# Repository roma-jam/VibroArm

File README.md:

# Vibro Watch
Contains fw and hw part of the vibro watch project.

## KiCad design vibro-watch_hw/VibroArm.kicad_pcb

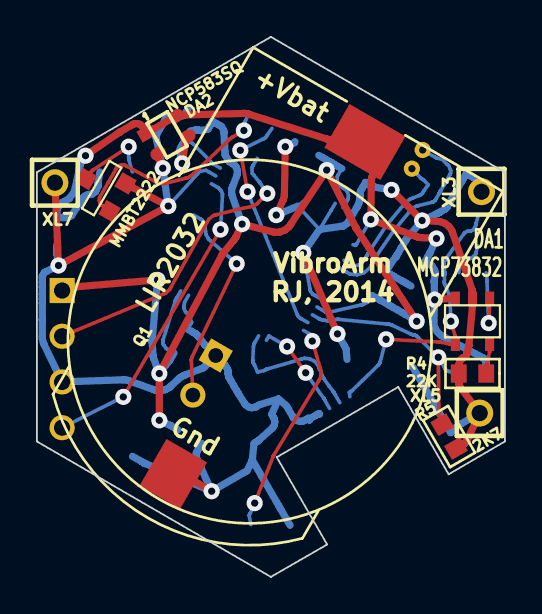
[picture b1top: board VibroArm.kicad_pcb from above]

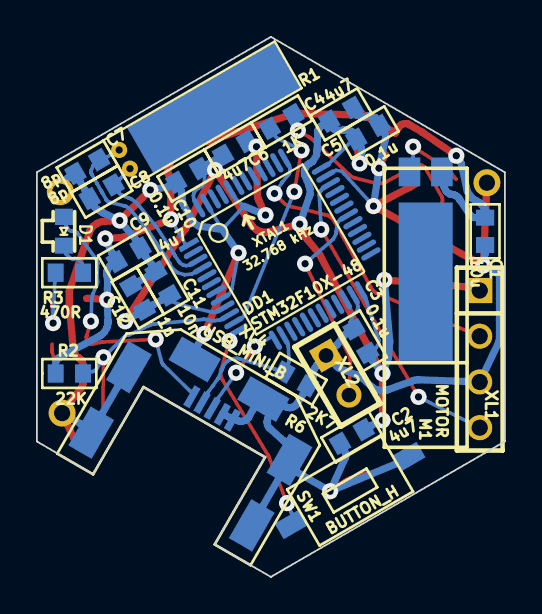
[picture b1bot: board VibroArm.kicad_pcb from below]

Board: 2 copper layers, 26.0 x 30.0 mm, 33 parts (24 on the bottom side), 19 nets.

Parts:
B1: BAT; BAT_CH7410
C1: 10u; CAP_0603
C2, C4, C6, C9: 4u7; CAP_0603
C3, C5, C10: 0.1u; CAP_0603
C7, C8: 8p; CAP_0603
C11: 10n; CAP_0603
C12: 1u; CAP_0603
D1: LED; LED_ANGLE
DA1: MCP73832; SOT23-5
DA2: NCP583SQ; SC82AB
DD1: STM32F10X-48; LQFP48
M1: MOTOR; MOTOR_KHN4NX
Q1: MMBT2222; SOT23
R1: 1K; RES_0603
R2, R4: 22K; RES_0603
R3: 470R; RES_0603
R5, R6: 2K7; RES_0603
SW1: BUTTON_H; BUTTON_IT1181A
XL1: ST_SWD; SIL-4
XL2: CONN_2; SIL-2
XL3, XL5, XL7: CONN_1; SIL-1
XL4: USB_MINI_B; USBmicro_MOLEX_WM17142
XTAL1: 32.768 kHz; CRYSTAL_KX38

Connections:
+3.3V: C2.1, C3.1, C4.1, C5.1, C6.1, C10.1, C11.1, C12.1, DA2.3, DD1.9, DD1.24, DD1.36, DD1.48, XL1.1
+BATT: B1.A, C1.1, C9.1, DA1.3, DA2.1, DA2.4, DD1.1, M1.2, R2.1
/ADC_IN: DD1.10, R2.2, R5.1
/Btn1: DD1.12, SW1.1
/SWCLK: DD1.37, XL1.2
/SWDIO: DD1.34, XL1.4
/USB_DM: DD1.14, R6.1, XL4.2
/USB_DP: DD1.13, XL4.3
GND: B1.C, C1.2, C2.2, C3.2, C4.2, C5.2, C6.2, C7.2, C8.2, C9.2, C10.2, C11.2, C12.2, DA1.2, DA2.2, DD1.8, DD1.23, DD1.35, DD1.44, DD1.47, Q1.2, R4.2, R5.2, R6.2, SW1.2, XL1.3, XL2.1, XL3.1, XL4.4, XL4.5, XL4.SHLD, XL5.1, XL7.1
unnamed: DD1.30, XL2.2
unnamed: DD1.11, R1.1
unnamed: C8.1, DD1.3, XTAL1.1
unnamed: Q1.1, R1.2
unnamed: M1.1, Q1.3
unnamed: C7.1, DD1.4, XTAL1.2
unnamed: D1.A, DA1.4, XL4.1
unnamed: D1.C, R3.1
unnamed: DA1.1, R3.2
unnamed: DA1.5, R4.1

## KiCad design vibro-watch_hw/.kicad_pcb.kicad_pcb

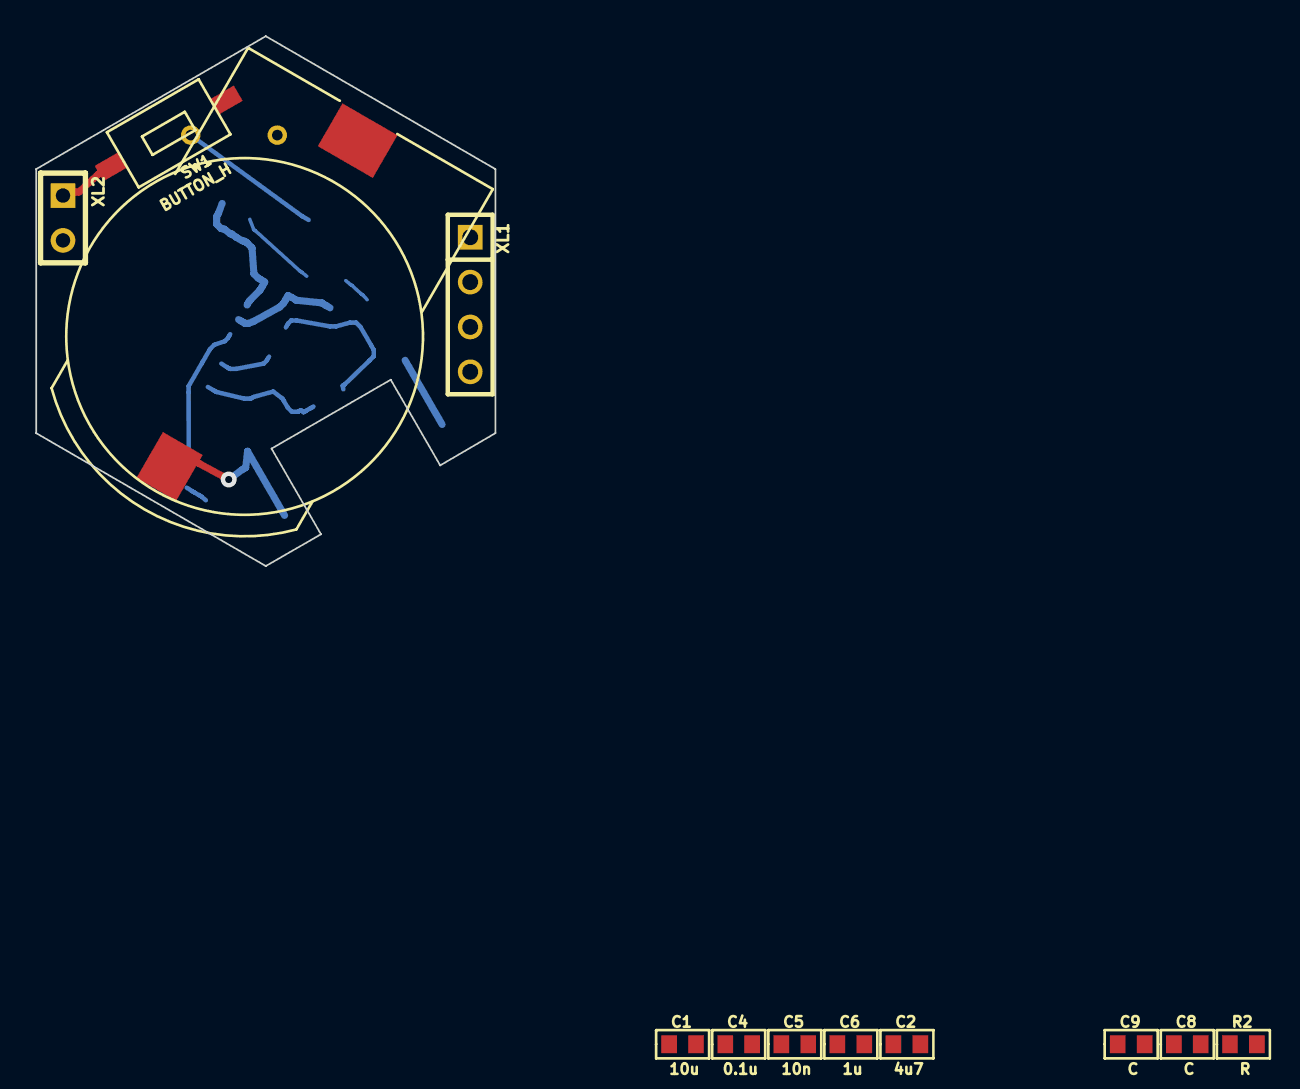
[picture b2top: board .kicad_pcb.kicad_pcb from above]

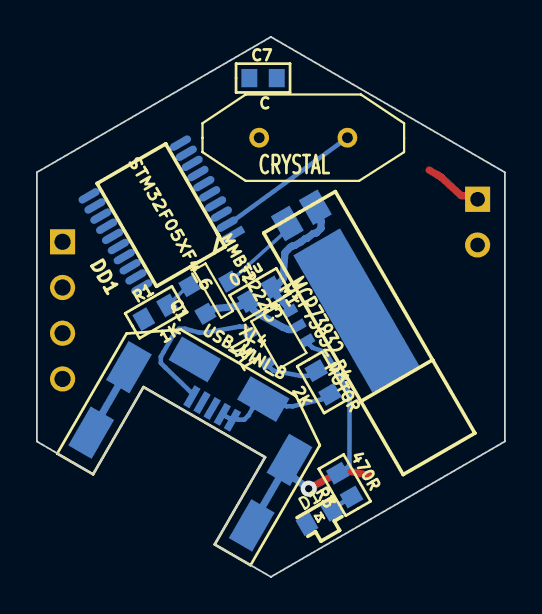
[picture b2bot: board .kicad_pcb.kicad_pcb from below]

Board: 2 copper layers, 26.0 x 30.0 mm, 24 parts (12 on the bottom side), 16 nets.

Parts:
B1: BAT; BAT_CH7410
C1: 10u; CAP_0603
C2: 4u7; CAP_0603
C3, C4: 0.1u; CAP_0603
C5: 10n; CAP_0603
C6: 1u; CAP_0603
C7, C8, C9: C; CAP_0603
D1: LED; LED_ANGLE
DA1: MCP73832; SOT23-5
DD1: STM32F05XF4_6; SSOP20
M1: MOTOR; MOTOR_KHN4NX
Q1: MMBT2222; SOT23
R1: 1K; RES_0603
R2: R; RES_0603
R3: 470R; RES_0603
R4: 2K; RES_0603
SW1: BUTTON_H; BUTTON_IT1181A
XL1: ST_SWD; SIL-4
XL2: CONN_2; SIL-2
XL4: USB_MINI_B; USBmicro_MOLEX_WM17142
XTAL1: CRYSTAL; CRYSTAL_HC49

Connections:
+BATT: B1.A, C1.1, C2.1, C3.1, C4.1, C5.1, C6.1, C9.1, DA1.3, DD1.5, DD1.16, M1.2, XL1.1
/Btn1: DD1.8, SW1.1
/SWCLK: DD1.20, XL1.2
/SWDIO: DD1.19, XL1.4
GND: B1.C, C1.2, C2.2, C3.2, C4.2, C5.2, C6.2, C7.2, C8.2, C9.2, DA1.2, DD1.1, DD1.15, Q1.2, R4.2, SW1.2, XL1.3, XL2.1, XL4.4, XL4.5, XL4.SHLD
unnamed: DD1.17, XL2.2
unnamed: DA1.5, R4.1
unnamed: DA1.1, R3.2
unnamed: D1.A, DA1.4, XL4.1
unnamed: D1.C, R3.1
unnamed: DD1.3, R2.1
unnamed: DD1.7, R1.1
unnamed: Q1.1, R1.2
unnamed: M1.1, Q1.3
unnamed: C7.1, R2.2, XTAL1.1
unnamed: C8.1, DD1.2, XTAL1.2

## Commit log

2015-08-06 Add hw part.
